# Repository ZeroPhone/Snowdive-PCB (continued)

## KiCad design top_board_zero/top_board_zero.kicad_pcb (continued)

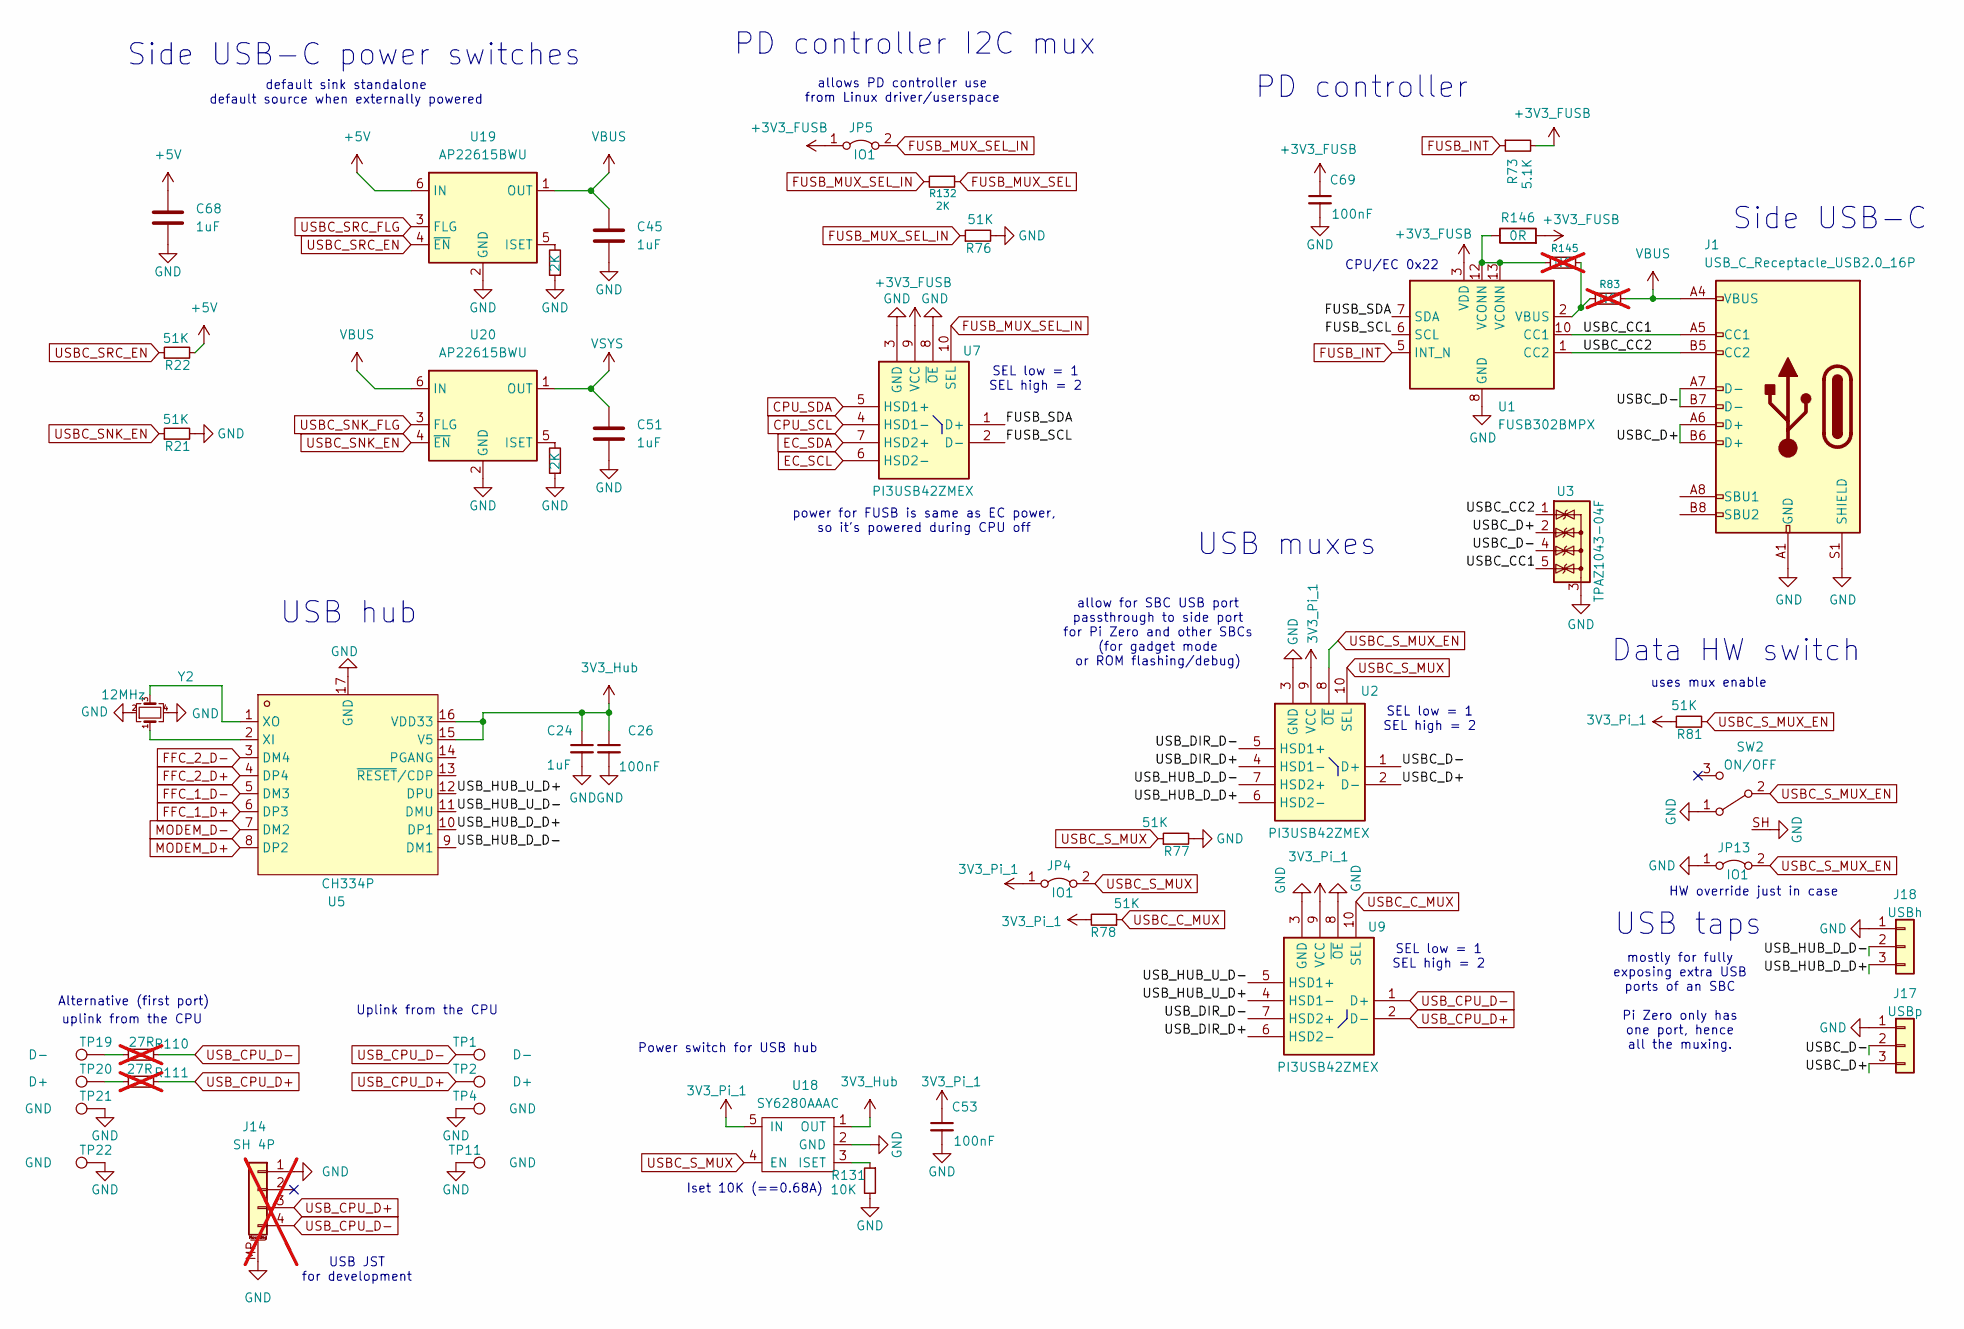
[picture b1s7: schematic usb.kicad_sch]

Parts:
C24: 1uF; C_0402_1005Metric; LCSC Part C52923
C26, C53, C69: 100nF; C_0402_1005Metric; LCSC Part C1525
C45, C51, C68: 1uF; C_0805_2012Metric_Pad1.18x1.45mm_HandSolder
J1: USB_C_Receptacle_USB2.0_16P; USB_C_Receptacle_HRO_TYPE-C-31-M-12; LCSC Part C165948
J14: SH 4P; JST_SH_SM04B-SRSS-TB_1x04-1MP_P1.00mm_Horizontal; LCSC Part C970137; not fitted
J17: USBp; PinHeader_1x03_P1.27mm_Vertical
J18: USBh; PinHeader_1x03_P1.27mm_Vertical
JP4, JP5, JP13: IO1; SolderJumper-2_smol_Open
R21, R22, R76, R77, R78, R81: 51K; R_0402_1005Metric; LCSC Part C25794
R73: 5.1K; R_0402_1005Metric; LCSC Part C25905
R83, R145: NC; R_0402_1005Metric; not fitted
R110, R111: 27R; R_0402_1005Metric; LCSC Part C25105; not fitted
R119, R120, R132: 2K; R_0402_1005Metric; LCSC Part C4109
R131: 10K; R_0402_1005Metric; LCSC Part C25744
R146: 0R; R_0402_1005Metric; LCSC Part C17168
SW2: ON/OFF; SW_SPDT_PCM12_SH; LCSC Part C431540
TP1, TP19: D-; TestPoint_Pad_1.0x1.0mm
TP2, TP20: D+; TestPoint_Pad_1.0x1.0mm
TP4, TP11, TP21, TP22: GND; TestPoint_Pad_1.0x1.0mm
U1: FUSB302BMPX; WQFN-14-1EP_2.5x2.5mm_P0.5mm_EP1.45x1.45mm
U2, U7, U9: PI3USB42ZMEX; QFN40P140X180X55-10N; Manufacturer_Part_Number FSUSB42UMX; Mouser Part Number 512-FSUSB42UMX
U3: TPAZ1043-04F; USON-10_2.5x1.0mm_P0.5mm
U5: CH334P; QFN-16-1EP_3x3mm_P0.5mm_EP1.7x1.7mm; LCSC Part C5373042
U18: SY6280AAAC; SOT-23-5; LCSC Part C207620
U19, U20: AP22615BWU; SOT-23-6
Y2: 12MHz; Crystal_SMD_3225-4Pin_3.2x2.5mm; LCSC Part C258938

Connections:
3V3_Hub: C24.1, C26.1, U5.15 (V5), U5.16 (VDD33), U18.1 (OUT); also elsewhere on the board
3V3_Pi_1: C53.1, JP4.1 (A), R78.2, R81.1, U2.9 (VCC), U9.9 (VCC), U18.5 (IN); also elsewhere on the board
+3V3_FUSB: C69.1, JP5.1 (A), R73.2, R146.2, U1.3 (VDD), U1.4 (VDD), U7.9 (VCC); also elsewhere on the board
+5V: C68.1, R22.2, U19.6 (IN); also elsewhere on the board
/USB/FUSB_SCL: U1.6 (SCL), U7.2 (D-)
/USB/FUSB_SDA: U1.7 (SDA), U7.1 (D+)
/USB/USBC_CC1: J1.A5 (CC1), U1.10 (CC1), U1.11 (CC1), U3.5 (IO4), U3.6 (NC)
/USB/USBC_CC2: J1.B5 (CC2), U1.1 (CC2), U1.14 (CC2), U3.1 (IO1), U3.10 (NC)
/USB/USBC_D+: J1.A6 (D+), J1.B6 (D+), J17.3, U2.2 (D-), U3.2 (IO2), U3.9 (NC)
/USB/USBC_D-: J1.A7 (D-), J1.B7 (D-), J17.2, U2.1 (D+), U3.4 (IO3), U3.7 (NC)
/USB/USB_DIR_D+: U2.4 (HSD1-), U9.6 (HSD2-)
/USB/USB_DIR_D-: U2.5 (HSD1+), U9.7 (HSD2+)
/USB/USB_HUB_D_D+: J18.3, U2.6 (HSD2-), U5.10 (DP1)
/USB/USB_HUB_D_D-: J18.2, U2.7 (HSD2+), U5.9 (DM1)
/USB/USB_HUB_U_D+: U5.12 (DPU), U9.4 (HSD1-)
/USB/USB_HUB_U_D-: U5.11 (DMU), U9.5 (HSD1+)
CPU_SCL: U7.4 (HSD1-); also elsewhere on the board
CPU_SDA: U7.5 (HSD1+); also elsewhere on the board
EC_SCL: U7.6 (HSD2-); also elsewhere on the board
EC_SDA: U7.7 (HSD2+); also elsewhere on the board
FFC_1_D+: U5.6 (DP3); also elsewhere on the board
FFC_1_D-: U5.5 (DM3); also elsewhere on the board
FFC_2_D+: U5.4 (DP4); also elsewhere on the board
FFC_2_D-: U5.3 (DM4); also elsewhere on the board
FUSB_INT: R73.1, U1.5 (INT_N); also elsewhere on the board
FUSB_MUX_SEL: R132.1; also elsewhere on the board
FUSB_MUX_SEL_IN: JP5.2 (B), R76.1, R132.2, U7.10 (SEL)
GND: C24.2, C26.2, C45.2, C51.2, C53.2, C68.2, C69.2, J1.A1 (GND), J1.A12 (GND), J1.B1 (GND), J1.B12 (GND), J1.S1 (SHIELD), J14.1, J14.MP (MountPin), J17.1, J18.1, JP13.1 (A), R21.2, R76.2, R77.2, R119.1, R120.1, R131.2, SW2.1 (A), SW2.SH, TP4.1 (1_1), TP11.1 (1_1), TP21.1 (1_1), TP22.1 (1_1), U1.8 (GND), U1.9 (GND), U1.15 (GND), U2.3 (GND), U3.3 (G), U3.8 (G), U5.17 (GND), U7.3 (GND), U7.8 (~OE), U9.3 (GND), U9.8 (~OE), U18.2 (GND), U19.2 (GND), U20.2 (GND), Y2.2, Y2.4; also elsewhere on the board
MODEM_D+: U5.8 (DP2); also elsewhere on the board
MODEM_D-: U5.7 (DM2); also elsewhere on the board
unnamed: R110.1, TP19.1 (1_1)
unnamed: R111.1, TP20.1 (1_1)
unnamed: R145.1, R146.1, U1.12 (VCONN), U1.13 (VCONN)
unnamed: R83.1, R145.2, U1.2 (VBUS)
unnamed: U5.2 (XI), Y2.1
unnamed: U5.1 (XO), Y2.3
unnamed: R131.1, U18.3 (ISET)
unnamed: R120.2, U19.5 (ISET)
unnamed: R119.2, U20.5 (ISET)
USBC_C_MUX: R78.1, U9.10 (SEL); also elsewhere on the board
USBC_SNK_EN: R21.1, U20.4 (~EN); also elsewhere on the board
USBC_SNK_FLG: U20.3 (FLG); also elsewhere on the board
USBC_SRC_EN: R22.1, U19.4 (~EN); also elsewhere on the board
USBC_SRC_FLG: U19.3 (FLG); also elsewhere on the board
USBC_S_MUX: JP4.2 (B), R77.1, U2.10 (SEL), U18.4 (EN); also elsewhere on the board
USBC_S_MUX_EN: JP13.2 (B), R81.2, SW2.2 (B), U2.8 (~OE)
USB_CPU_D+: J14.3, R111.2, TP2.1 (1_1), U9.2 (D-)
USB_CPU_D-: J14.4, R110.2, TP1.1 (1_1), U9.1 (D+)
VBUS: C45.1, J1.A4 (VBUS), J1.A9 (VBUS), J1.B4 (VBUS), J1.B9 (VBUS), R83.2, U19.1 (OUT), U20.6 (IN)
VSYS: C51.1, U20.1 (OUT); also elsewhere on the board

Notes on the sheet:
allow for SBC USB port passthrough to side port for Pi Zero and other SBCs (for gadget mode or ROM flashing/debug)
CPU/EC 0x22
USB taps
PD controller
Power switch for USB hub
Side USB-C
Uplink from the CPU
SEL low = 1 SEL high = 2
Side USB-C power switches
default sink standalone default source when externally powered
PD controller I2C mux
allows PD controller use from Linux driver/userspace
Data HW switch
uses mux enable
mostly for fully exposing extra USB ports of an SBC Pi Zero only has one port, hence all the muxing.
Alternative (first port)
USB muxes
HW override just in case
USB hub
USB JST for development
power for FUSB is same as EC power, so it's powered during CPU off
uplink from the CPU
Iset 10K (==0.68A)

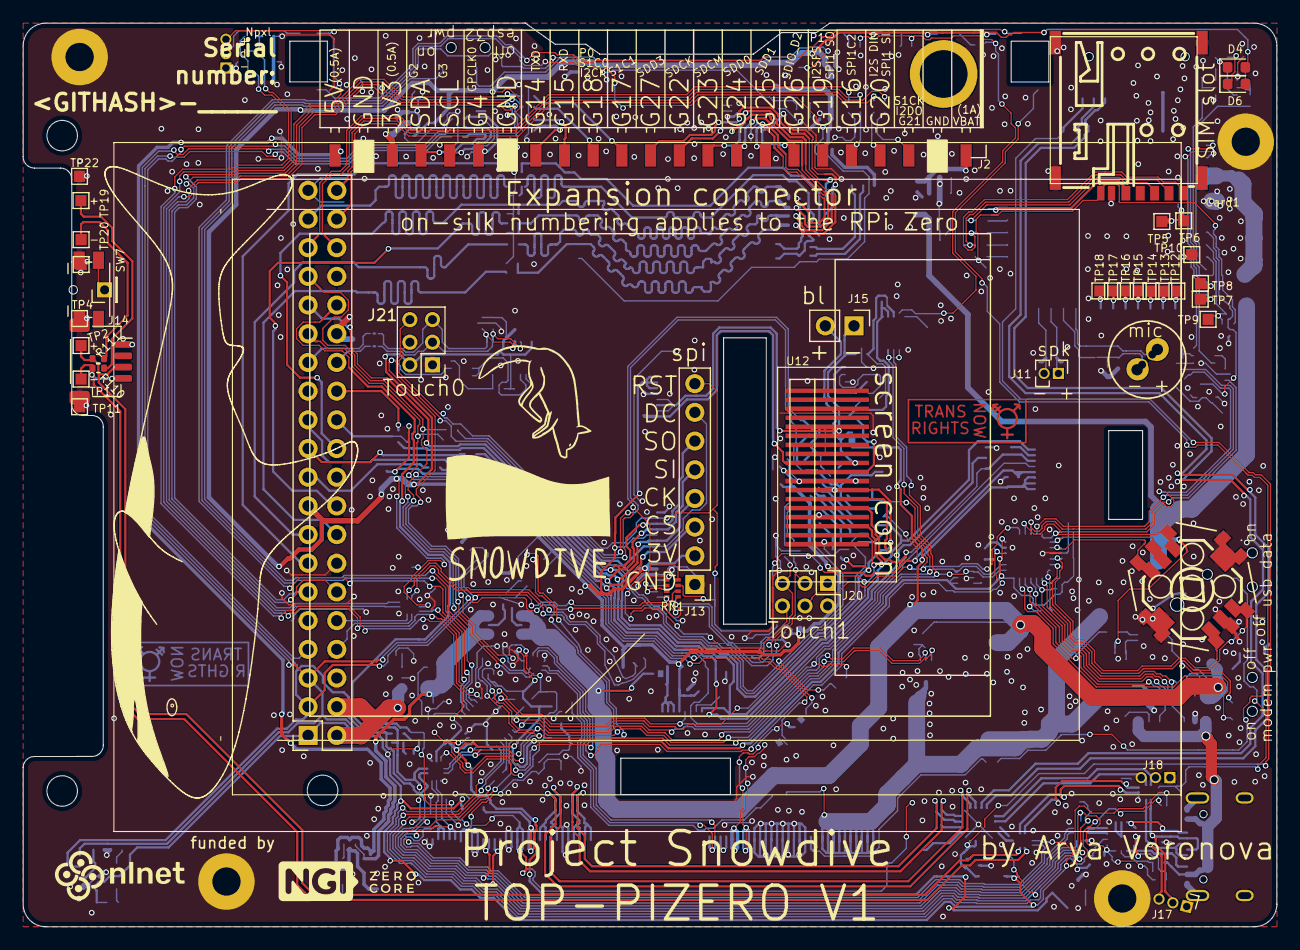
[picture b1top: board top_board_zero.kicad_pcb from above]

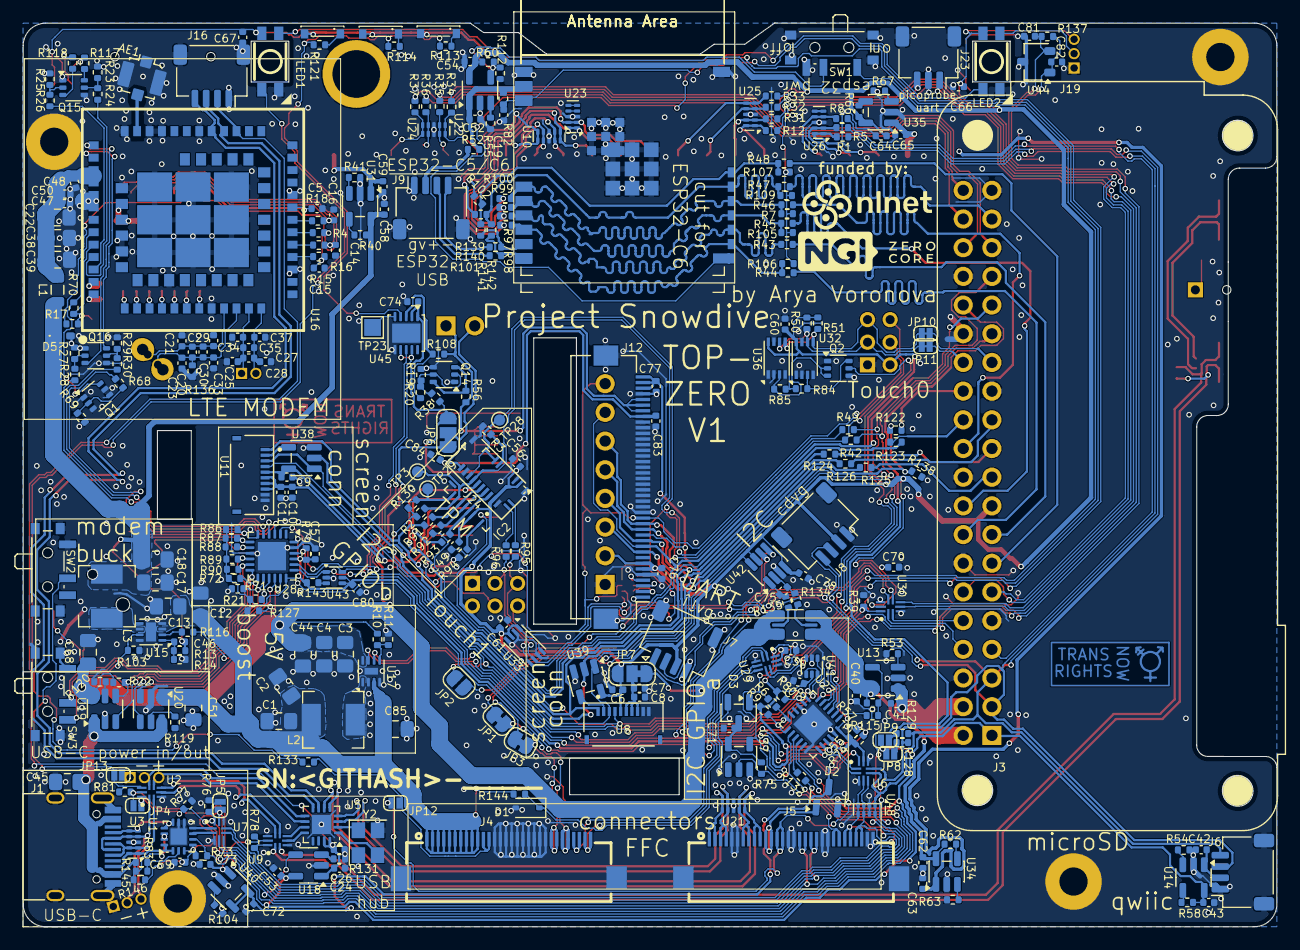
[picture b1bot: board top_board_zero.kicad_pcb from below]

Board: 4 copper layers, 111.0 x 80.0 mm, 372 parts (323 on the bottom side), 260 nets.

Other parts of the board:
TRNSRTS: Trans Rights now Front
TRNSRTS#2: Trans Rights now Back

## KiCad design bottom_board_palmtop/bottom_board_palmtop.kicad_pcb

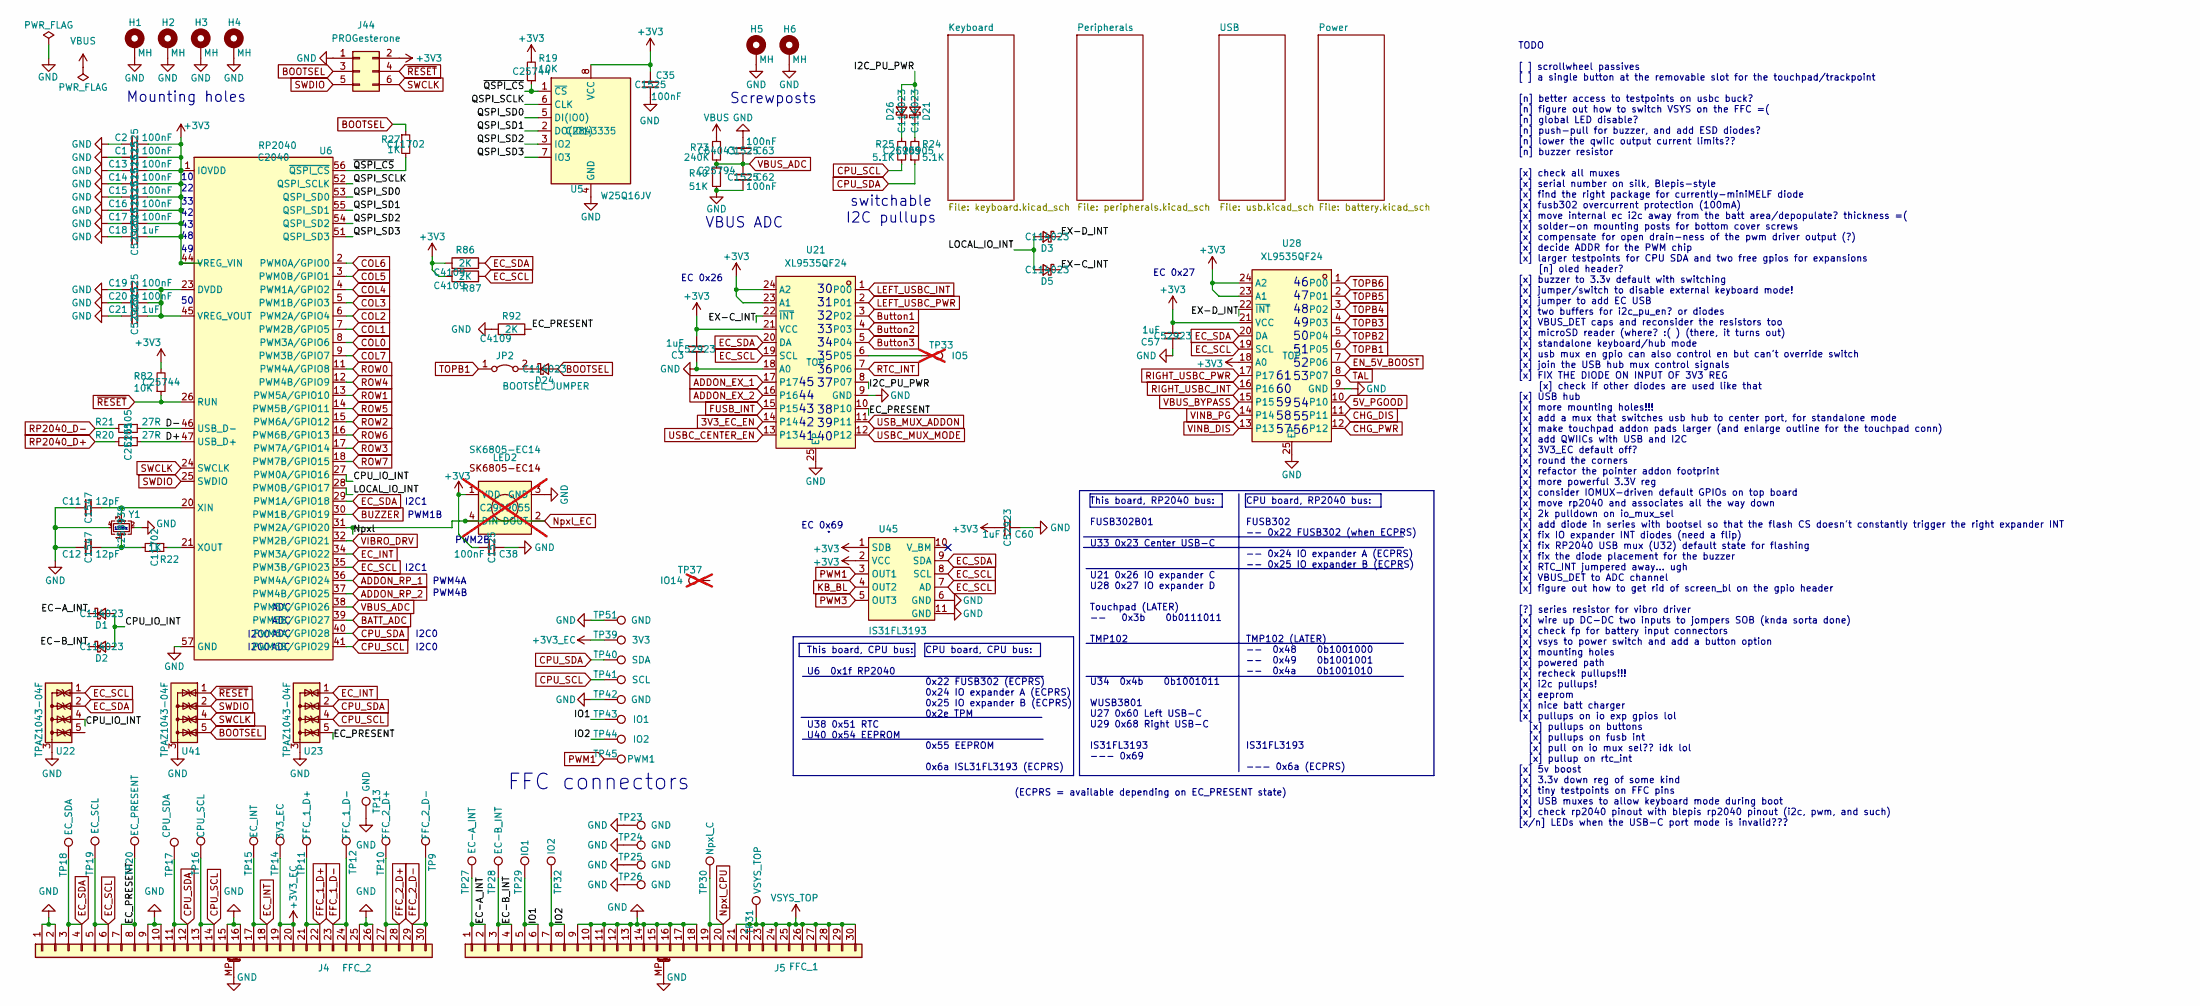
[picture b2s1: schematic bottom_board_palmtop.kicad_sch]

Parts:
C1, C2, C13, C14, C15, C16, C17, C19, C20, C35, C38, C62, C63: 100nF; C_0402_1005Metric; LCSC Part C1525
C3, C18, C21, C57, C60: 1uF; C_0402_1005Metric; LCSC Part C52923
C11, C12: 12pF; C_0402_1005Metric; LCSC Part C1547
D1, D2, D3, D5, D21, D24, D26: D_Schottky_Small; D_SOD-323; LCSC Part C114023
H1, H2, H3, H4: MH; MountingHole_2.5mm_Pad
H5, H6: MH; MountingHole_2.5mm_Pad-paste
J4: FFC_2; FPC-SMD_30P-P0.50_XF3M-3015-1B; LCSC Part C5700582
J5: FFC_1; FPC-SMD_30P-P0.50_XF3M-3015-1B; LCSC Part C5700582
J44: PROGesterone; PinHeader_2x03_P2.54mm_Vertical_PROG
JP2: BOOTSEL_JUMPER; SolderJumper-2_P1.3mm_Bridged_RoundedPad1.0x1.5mm
LED2: SK6805-EC14; LCSC Part C2909055; not fitted
R19, R82: 10K; R_0402_1005Metric; LCSC Part C25744
R20, R21: 27R; R_0402_1005Metric; LCSC Part C25105
R22, R27: 1K; R_0402_1005Metric; LCSC Part C11702
R24, R25: 5.1K; R_0402_1005Metric; LCSC Part C25905
R40: 51K; R_0402_1005Metric; LCSC Part C25794
R73: 240K; R_0402_1005Metric; LCSC Part C64043
R86, R87, R92: 2K; R_0402_1005Metric; LCSC Part C4109
TP9: FFC_2_D-; TestPoint_Pad_0.6x0.6mm
TP10: FFC_2_D+; TestPoint_Pad_0.6x0.6mm
TP11: FFC_1_D+; TestPoint_Pad_0.6x0.6mm
TP12: FFC_1_D-; TestPoint_Pad_0.6x0.6mm
TP13, TP23, TP24, TP25, TP26: GND; TestPoint_Pad_0.6x0.6mm
TP14: 3V3_EC; TestPoint_Pad_0.6x0.6mm
TP15: EC_INT; TestPoint_Pad_0.6x0.6mm
TP16: CPU_SCL; TestPoint_Pad_0.6x0.6mm
TP17: CPU_SDA; TestPoint_Pad_0.6x0.6mm
TP18: EC_SDA; TestPoint_Pad_0.6x0.6mm
TP19: EC_SCL; TestPoint_Pad_0.6x0.6mm
TP20: EC_PRESENT; TestPoint_Pad_0.6x0.6mm
TP27: EC-A_INT; TestPoint_Pad_0.6x0.6mm
TP28: EC-B_INT; TestPoint_Pad_0.6x0.6mm
TP29: IO1; TestPoint_Pad_0.6x0.6mm
TP30: Npxl_C; TestPoint_Pad_0.6x0.6mm
TP31: VSYS_TOP; TestPoint_Pad_0.6x0.6mm
TP32: IO2; TestPoint_Pad_0.6x0.6mm
TP33: IO5; TestPoint_Pad_0.6x0.6mm; not fitted
TP37: IO14; TestPoint_Pad_0.6x0.6mm; not fitted
TP39: 3V3; TestPoint_Pad_1.5x1.5mm
TP40: SDA; TestPoint_Pad_1.5x1.5mm
TP41: SCL; TestPoint_Pad_1.5x1.5mm
TP42, TP51: GND; TestPoint_Pad_1.5x1.5mm
TP43: IO1; TestPoint_Pad_1.5x1.5mm
TP44: IO2; TestPoint_Pad_1.5x1.5mm
TP45: PWM1; TestPoint_Pad_1.5x1.5mm
U5: W25Q16JV; DFN-8-1EP_3x2mm_P0.5mm_EP1.3x1.5mm; LCSC Part C2843335
U6: RP2040; QFN-56-1EP_7x7mm_P0.4mm_EP5.6x5.6mm; LCSC Part C2040
U21, U28: XL9535QF24; QFN-24-1EP_4x4mm_P0.5mm_EP2.5x2.5mm; LCSC Part C5444301
U22, U23, U41: TPAZ1043-04F; USON-10_2.5x1.0mm_P0.5mm
U45: IS31FL3193; DFN-10-1EP_3x3mm_P0.5mm_EP1.7x2.5mm
Y1: 12MHz; Crystal_SMD_3225-4Pin_3.2x2.5mm; LCSC Part C258938

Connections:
3V3_EC_EN: U21.14; also elsewhere on the board
5V_PGOOD: U28.10; also elsewhere on the board
+3V3: C1.1, C2.1, C3.1, C13.1, C14.1, C15.1, C16.1, C17.1, C18.1, C35.1, C38.1, C57.1, C60.1, J44.2, LED2.1 (VDD), R19.2, R82.2, R86.1, R87.1, U5.8 (VCC), U6.1 (IOVDD), U6.10 (IOVDD), U6.22 (IOVDD), U6.33 (IOVDD), U6.42 (IOVDD), U6.43 (ADC_AVDD), U6.44 (VREG_VIN), U6.48 (USB_VDD), U6.49 (IOVDD), U21.21 (VCC), U21.23 (A1), U21.24 (A2), U28.18 (A0), U28.21 (VCC), U28.23 (A1), U28.24 (A2), U45.1 (SDB), U45.2 (VCC); also elsewhere on the board
+3V3_EC: J4.19, J4.20, TP14.1, TP39.1; also elsewhere on the board
/CPU_IO_INT: D1.2 (A), D2.2 (A), U6.27 (PWM0A/GPIO16), U22.4 (IO3), U22.7 (NC)
/D+: R20.1, U6.47 (USB_D+)
/D-: R21.1, U6.46 (USB_D-)
/EC-A_INT: D1.1 (K), J5.1, J5.2, TP27.1
/EC-B_INT: D2.1 (K), J5.3, J5.4, TP28.1
/EC_PRESENT: J4.7, J4.8, R92.2, TP20.1, U21.10, U23.5 (IO4), U23.6 (NC)
/EX-C_INT: D5.1 (K), U21.22 (~INT)
/EX-D_INT: D3.1 (K), U28.22 (~INT)
/I2C_PU_PWR: D21.2 (A), D26.2 (A), U21.8 (P07)
/IO1: J5.5, J5.6, TP29.1, TP43.1
/IO2: J5.7, J5.8, TP32.1, TP44.1
/LOCAL_IO_INT: D3.2 (A), D5.2 (A), U6.28 (PWM0B/GPIO17)
/QSPI_SCLK: U5.6 (CLK), U6.52 (QSPI_SCLK)
/QSPI_SD0: U5.5 (DI(IO0)), U6.53 (QSPI_SD0)
/QSPI_SD1: U5.2 (DO(IO1)), U6.55 (QSPI_SD1)
/QSPI_SD2: U5.3 (IO2), U6.54 (QSPI_SD2)
/QSPI_SD3: U5.7 (IO3), U6.51 (QSPI_SD3)
/~QSPI_CS: R19.1, R27.2, U5.1 (~CS), U6.56 (~QSPI_CS)
ADDON_EX_1: U21.17; also elsewhere on the board
ADDON_EX_2: U21.16; also elsewhere on the board
ADDON_RP_1: U6.36 (PWM4A/GPIO24); also elsewhere on the board
ADDON_RP_2: U6.37 (PWM4B/GPIO25); also elsewhere on the board
BATT_ADC: U6.39 (PWM5B/GPIO27); also elsewhere on the board
BOOTSEL: D24.2 (A), J44.3, R27.1, U41.5 (IO4), U41.6 (NC)
BUZZER: U6.30 (PWM1B/GPIO19); also elsewhere on the board
Button1: U21.3 (P02); also elsewhere on the board
Button2: U21.4 (P03); also elsewhere on the board
Button3: U21.5 (P04); also elsewhere on the board
CHG_DIS: U28.11; also elsewhere on the board
CHG_PWR: U28.12; also elsewhere on the board
COL0: U6.8 (PWM3A/GPIO6); also elsewhere on the board
COL1: U6.7 (PWM2B/GPIO5); also elsewhere on the board
COL2: U6.6 (PWM2A/GPIO4); also elsewhere on the board
COL3: U6.5 (PWM1B/GPIO3); also elsewhere on the board
COL4: U6.4 (PWM1A/GPIO2); also elsewhere on the board
COL5: U6.3 (PWM0B/GPIO1); also elsewhere on the board
COL6: U6.2 (PWM0A/GPIO0); also elsewhere on the board
COL7: U6.9 (PWM3B/GPIO7); also elsewhere on the board
CPU_SCL: J4.13, J4.14, R25.2, TP16.1, TP41.1, U6.41 (PWM6B/GPIO29), U23.4 (IO3), U23.7 (NC); also elsewhere on the board
CPU_SDA: J4.11, J4.12, R24.1, TP17.1, TP40.1, U6.40 (PWM6A/GPIO28), U23.2 (IO2), U23.9 (NC); also elsewhere on the board
EC_INT: J4.17, J4.18, TP15.1, U6.34 (PWM3A/GPIO22), U23.1 (IO1), U23.10 (NC)
EC_SCL: J4.5, J4.6, R87.2, TP19.1, U6.35 (PWM3B/GPIO23), U21.19 (SCL), U22.1 (IO1), U22.10 (NC), U28.19 (SCL), U45.7 (AD), U45.8 (SCL); also elsewhere on the board
EC_SDA: J4.3, J4.4, R86.2, TP18.1, U6.29 (PWM1A/GPIO18), U21.20 (DA), U22.2 (IO2), U22.9 (NC), U28.20 (DA), U45.9 (SDA); also elsewhere on the board
EN_5V_BOOST: U28.7 (P06); also elsewhere on the board
FFC_1_D+: J4.21, J4.22, TP11.1; also elsewhere on the board
FFC_1_D-: J4.23, J4.24, TP12.1; also elsewhere on the board
FFC_2_D+: J4.27, J4.28, TP10.1; also elsewhere on the board
FFC_2_D-: J4.29, J4.30, TP9.1; also elsewhere on the board
FUSB_INT: U21.15; also elsewhere on the board
GND: C1.2, C2.2, C3.2, C11.2, C12.2, C13.2, C14.2, C15.2, C16.2, C17.2, C18.2, C19.2, C20.2, C21.2, C35.2, C38.2, C57.2, C60.2, C62.2, C63.2, H1.1, H2.1, H3.1, H4.1, H5.1, H6.1, J4.1, J4.2, J4.9, J4.10, J4.15, J4.16, J4.25, J4.26, J4.MP (MountPin), J5.9, J5.10, J5.11, J5.12, J5.13, J5.14, J5.15, J5.16, J5.17, J5.18, J5.MP (MountPin), J44.1, LED2.3 (GND), R40.2, R92.1, TP13.1, TP23.1, TP24.1, TP25.1, TP26.1, TP42.1, TP51.1, U5.4 (GND), U6.19 (TESTEN), U6.57 (GND), U21.9 (GND), U21.18 (A0), U21.25 (EP), U22.3 (G), U22.8 (G), U23.3 (G), U23.8 (G), U28.9 (GND), U28.25 (EP), U41.3 (G), U41.8 (G), U45.6 (GND), U45.11 (GND), Y1.2, Y1.4; also elsewhere on the board
KB_BL: U45.4 (OUT2); also elsewhere on the board
LEFT_USBC_INT: U21.1 (P00); also elsewhere on the board
LEFT_USBC_PWR: U21.2 (P01); also elsewhere on the board
unnamed: C12.1, R22.2, Y1.1
unnamed: D21.1 (K), R24.2
unnamed: D24.1 (K), JP2.2 (B)
unnamed: D26.1 (K), R25.1
unnamed: C19.1, C20.1, C21.1, U6.23 (DVDD), U6.45 (VREG_VOUT), U6.50 (DVDD)
unnamed: C11.1, U6.20 (XIN), Y1.3
unnamed: R22.1, U6.21 (XOUT)
unnamed: TP33.1, U21.6 (P05)
unnamed: U22.5 (IO4), U22.6 (NC)
Npxl_CPU: J5.19, J5.20, TP30.1; also elsewhere on the board
Npxl_EC: LED2.2 (DOUT), LED2.4 (DIN), U6.31 (PWM2A/GPIO20); also elsewhere on the board
PWM1: TP45.1, U45.3 (OUT1)
PWM3: U45.5 (OUT3); also elsewhere on the board
RIGHT_USBC_INT: U28.16; also elsewhere on the board
RIGHT_USBC_PWR: U28.17; also elsewhere on the board
ROW0: U6.11 (PWM4A/GPIO8); also elsewhere on the board
ROW1: U6.13 (PWM5A/GPIO10); also elsewhere on the board
ROW2: U6.15 (PWM6A/GPIO12); also elsewhere on the board
ROW3: U6.17 (PWM7A/GPIO14); also elsewhere on the board
ROW4: U6.12 (PWM4B/GPIO9); also elsewhere on the board
ROW5: U6.14 (PWM5B/GPIO11); also elsewhere on the board
ROW6: U6.16 (PWM6B/GPIO13); also elsewhere on the board
ROW7: U6.18 (PWM7B/GPIO15); also elsewhere on the board
RP2040_D+: R20.2; also elsewhere on the board
RP2040_D-: R21.2; also elsewhere on the board
RTC_INT: U21.7 (P06); also elsewhere on the board
SWCLK: J44.6, U6.24 (SWCLK), U41.4 (IO3), U41.7 (NC)
SWDIO: J44.5, U6.25 (SWDIO), U41.2 (IO2), U41.9 (NC)
TAL: U28.8 (P07); also elsewhere on the board
TOPB1: JP2.1 (A), U28.6 (P05); also elsewhere on the board
TOPB2: U28.5 (P04); also elsewhere on the board
TOPB3: U28.4 (P03); also elsewhere on the board
TOPB4: U28.3 (P02); also elsewhere on the board
TOPB5: U28.2 (P01); also elsewhere on the board
TOPB6: U28.1 (P00); also elsewhere on the board
USBC_CENTER_EN: U21.13; also elsewhere on the board
USBC_MUX_MODE: U21.12; also elsewhere on the board
USB_MUX_ADDON: U21.11; also elsewhere on the board
VBUS: R73.1; also elsewhere on the board
VBUS_ADC: C62.1, C63.1, R40.1, R73.2, U6.38 (PWM5A/GPIO26)
VBUS_BYPASS: U28.15; also elsewhere on the board
VIBRO_DRV: U6.32 (PWM2B/GPIO21); also elsewhere on the board
VINB_DIS: U28.13; also elsewhere on the board
VINB_PG: U28.14; also elsewhere on the board
VSYS_TOP: J5.21, J5.22, J5.23, J5.24, J5.25, J5.26, J5.27, J5.28, J5.29, J5.30, TP31.1; also elsewhere on the board
~RESET: J44.4, R82.1, U6.26 (RUN), U41.1 (IO1), U41.10 (NC)

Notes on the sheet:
EC 0x26
ADC
Mounting holes
PWM4B
PWM1B
I2C0
switchable I2C pullups
PWM4A
46 47 48 49 50 51 52 53 54 55 56
EC 0x69
30 31 32 33 34 35 36 37 38 39 40
(ECPRS = available depending on EC_PRESENT state)
This board, RP2040 bus: FUSB302B01 U33 0x23 Center USB-C U21 0x26 IO expander C U28 0x27 IO expander D Touchpad (LATER) -- 0x3b 0b0111011 TMP102 U34 0x4b 0b1001011 WUSB3801 U27 0x60 Left USB-C U29 0x68 Right USB-C IS31FL3193 --- 0x69
I2C0
FFC connectors
VBUS ADC
PWM2B
Screwposts
This board, CPU bus: U6 0x1f RP2040 U38 0x51 RTC U40 0x54 EEPROM
EC 0x27
TODO [ ] scrollwheel passives [ ] a single button at the removable slot for the touchpad/trackpoint [n] better access to testpoints on usbc buck? [n] figure out how to switch VSYS on the FFC =( [n] global LED disable? [n] push-pull for buzzer, and add ESD diodes? [n] lower the qwiic output current 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
CPU board, CPU bus: 0x22 FUSB302 (ECPRS) 0x24 IO expander A (ECPRS) 0x25 IO expander B (ECPRS) 0x2e TPM 0x55 EEPROM 0x6a ISL31FL3193 (ECPRS)
61 60 59 58 57
I2C1
45 44 43 42 41
12MHz
CPU board, RP2040 bus: FUSB302 -- 0x22 FUSB302 (when ECPRS) -- 0x24 IO expander A (ECPRS) -- 0x25 IO expander B (ECPRS) TMP102 (LATER) -- 0x48 0b1001000 -- 0x49 0b1001001 -- 0x4a 0b1001010 IS31FL3193 --- 0x6a (ECPRS)
nice

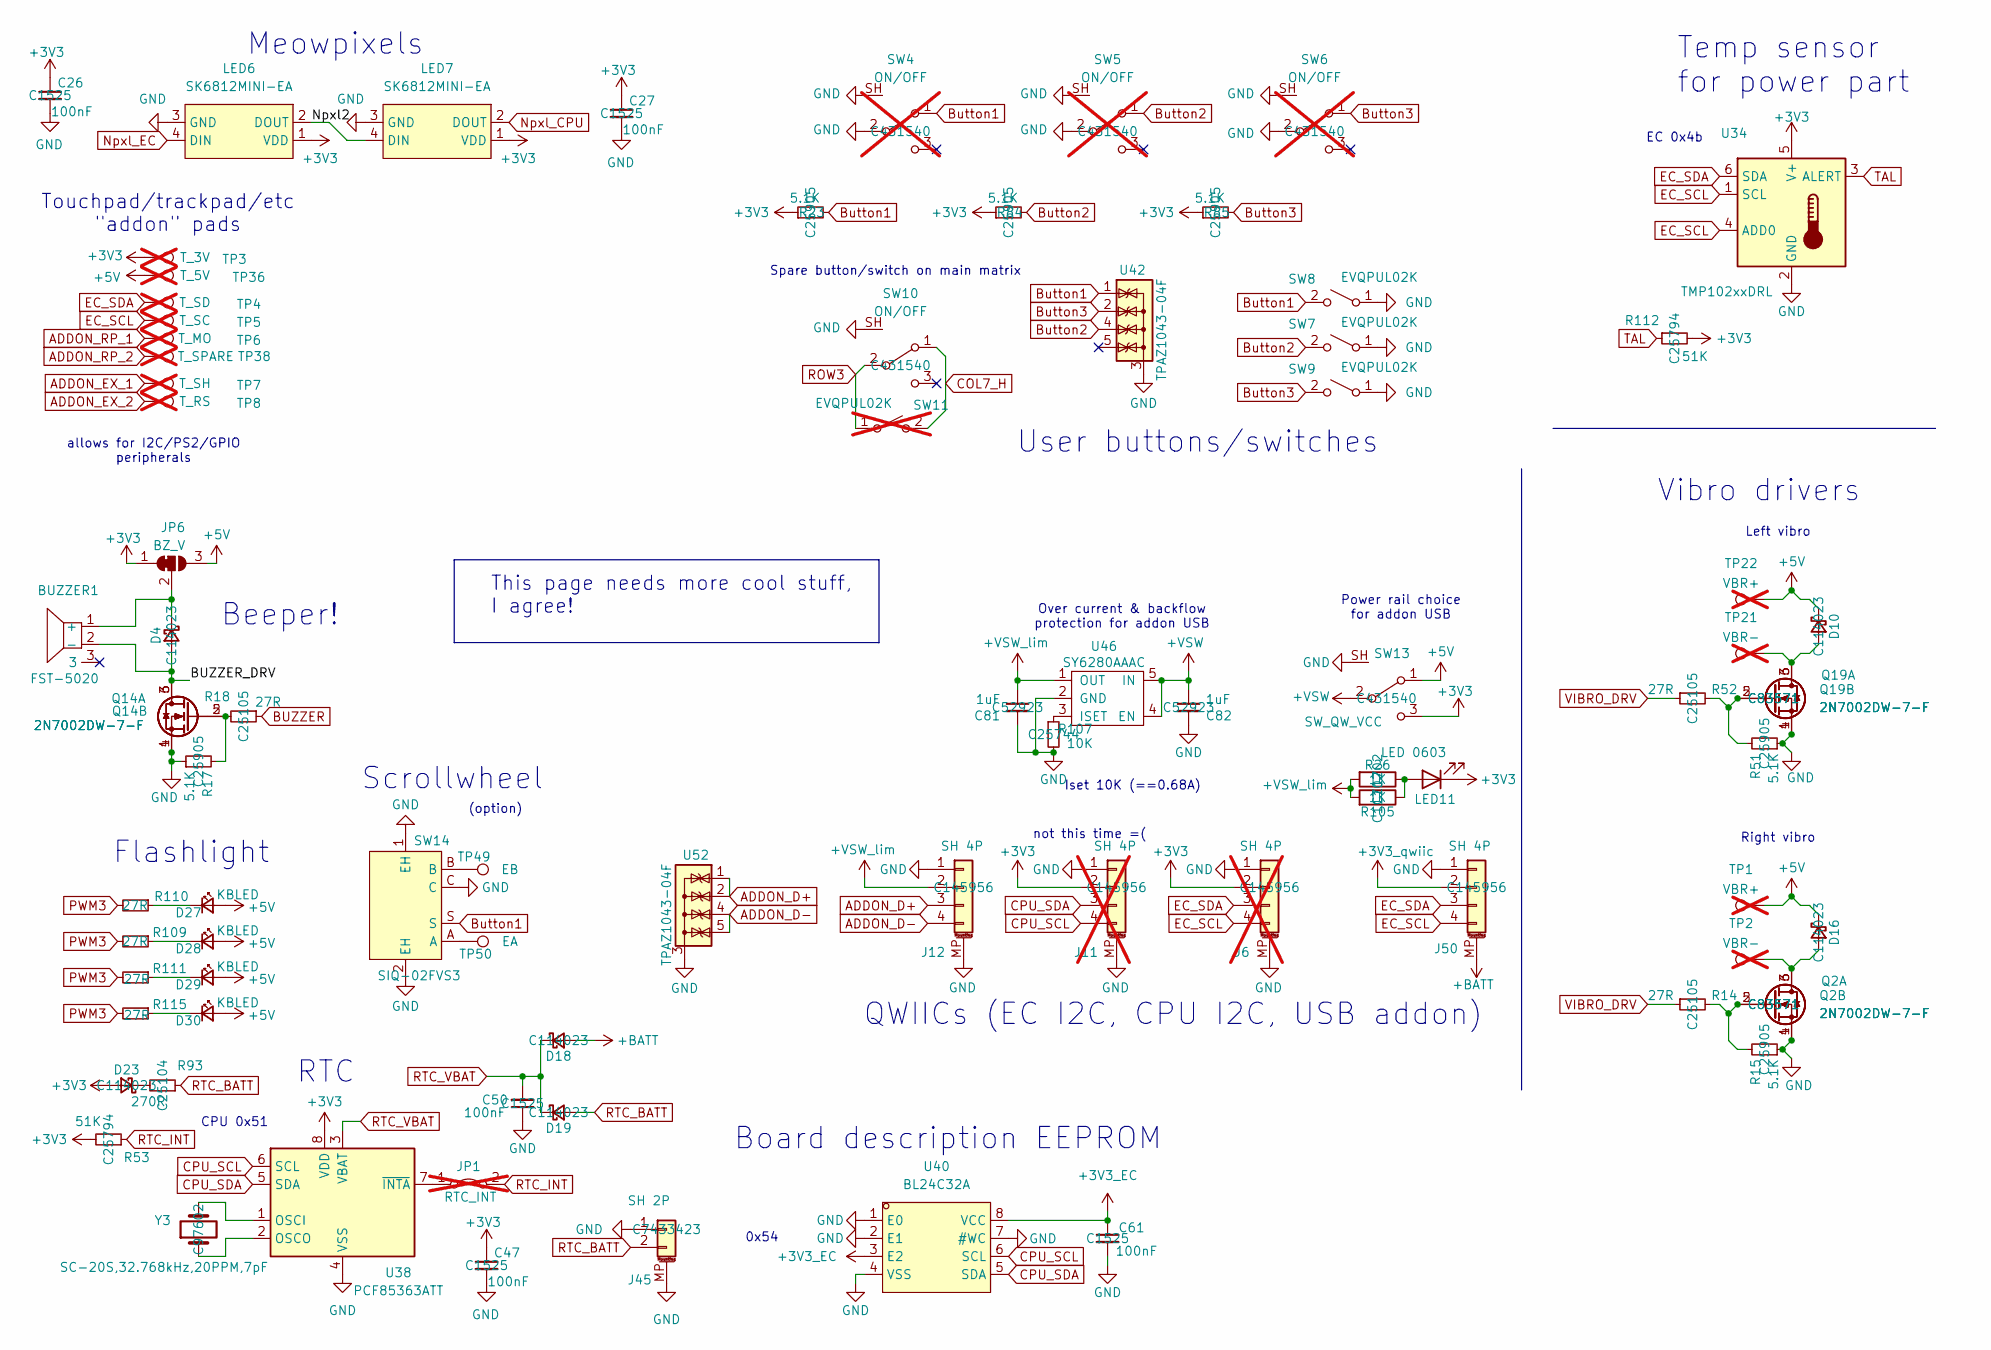
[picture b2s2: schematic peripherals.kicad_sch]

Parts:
BUZZER1: FST-5020; BUZ-SMD_FST-5020; LCSC Part C391029
C26, C27, C47, C50, C61: 100nF; C_0402_1005Metric; LCSC Part C1525
C81, C82: 1uF; C_0402_1005Metric; LCSC Part C52923
D4, D10, D16, D18, D19, D23: D_Schottky_Small; D_SOD-323; LCSC Part C114023
D27, D28, D29, D30: KBLED; LTW-010DCG
J6, J11: SH 4P; JST_SH_SM04B-SRSS-TB_1x04-1MP_P1.00mm_Horizontal; LCSC Part C145956; not fitted
J12, J50: SH 4P; JST_SH_SM04B-SRSS-TB_1x04-1MP_P1.00mm_Horizontal; LCSC Part C145956
J45: SH 2P; JST_SH_BM02B-SRSS-TB_1x02-1MP_P1.00mm_Vertical; LCSC Part C7433423
JP1: RTC_INT; SolderJumper-2_smol_Open; not fitted
JP6: BZ_V; SolderJumper-3_P1.3mm_Bridged12_RoundedPad1.0x1.5mm
LED6, LED7: SK6812MINI-EA; LED-SMD_4P-L3.2-W2.8_SK6812MINI-EA; LCSC Part C5378731
LED11: LED 0603; LED_0603_1608Metric; LCSC Part C5151483
Q2, Q14, Q19: 2N7002DW-7-F; SOT-363_SC-70-6; LCSC Part C83571
R14, R18, R52, R109, R110, R111, R115: 27R; R_0402_1005Metric; LCSC Part C25105
R15, R17, R23, R51, R84, R85: 5.1K; R_0402_1005Metric; LCSC Part C25905
R26, R105: 1K; R_0402_1005Metric; LCSC Part C11702
R53, R112: 51K; R_0402_1005Metric; LCSC Part C25794
R93: 270R; R_0402_1005Metric; LCSC Part C25104
R107: 10K; R_0402_1005Metric; LCSC Part C25744
SW4, SW5, SW6: ON/OFF; SW_SPDT_PCM12_SH; LCSC Part C431540; not fitted
SW7, SW8, SW9: EVQPUL02K; Panasonic_EVQPUL_EVQPUC
SW10: ON/OFF; SW_SPDT_PCM12_SH; LCSC Part C431540
SW11: EVQPUL02K; Panasonic_EVQPUL_EVQPUC; not fitted
SW13: SW_QW_VCC; SW_SPDT_PCM12_SH; LCSC Part C431540
SW14: SIQ-02FVS3; SW-SMD_SIQ-02FVS3; MPN SIQ-02FVS3; LCSC Part C29780879
TP1, TP22: VBR+; TestPoint_Pad_1.0x1.0mm; not fitted
TP2, TP21: VBR-; TestPoint_Pad_1.0x1.0mm; not fitted
TP3: T_3V; TestPoint_Pad_1.0x1.0mm; not fitted
TP4: T_SD; TestPoint_Pad_1.0x1.0mm; not fitted
TP5: T_SC; TestPoint_Pad_1.0x1.0mm; not fitted
TP6: T_MO; TestPoint_Pad_1.0x1.0mm; not fitted
TP7: T_SH; TestPoint_Pad_1.0x1.0mm; not fitted
TP8: T_RS; TestPoint_Pad_1.0x1.0mm; not fitted
TP36: T_5V; TestPoint_Pad_1.0x1.0mm; not fitted
TP38: T_SPARE; TestPoint_Pad_1.0x1.0mm; not fitted
TP49: EB; TestPoint_Pad_1.5x1.5mm
TP50: EA; TestPoint_Pad_1.5x1.5mm
U34: TMP102xxDRL; SOT-563; LCSC Part C99269
U38: PCF85363ATT; TSSOP-8_3x3mm_P0.65mm
U40: BL24C32A; DFN-8-1EP_3x2mm_P0.5mm_EP1.3x1.5mm; LCSC Part C691878
U42, U52: TPAZ1043-04F; USON-10_2.5x1.0mm_P0.5mm
U46: SY6280AAAC; SOT-23-5; LCSC Part C207620
Y3: SC-20S,32.768kHz,20PPM,7pF; Crystal_SMD_TXC_9HT11-2Pin_2.0x1.2mm; LCSC Part C97602

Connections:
+3V3: C26.1, C27.1, C47.1, D23.2 (A), J6.2, J11.2, JP6.1 (A), LED6.1 (VDD), LED7.1 (VDD), LED11.1 (K), R23.1, R53.2, R84.1, R85.1, R112.2, SW13.3 (C), TP3.1, U34.5 (V+), U38.8 (VDD); also elsewhere on the board
+3V3_EC: C61.1, U40.3 (E2), U40.8 (VCC); also elsewhere on the board
+3V3_qwiic: J50.2; also elsewhere on the board
+5V: D10.1 (K), D16.1 (K), D27.2 (A), D28.2 (A), D29.2 (A), D30.2 (A), JP6.3 (B), SW13.1 (A), TP1.1, TP22.1, TP36.1; also elsewhere on the board
+BATT: D18.2 (A), J50.MP (MountPin); also elsewhere on the board
+VSW: C82.1, SW13.2 (B), U46.4 (EN), U46.5 (IN)
+VSW_lim: C81.1, J12.2, R26.2, R105.2, U46.1 (OUT)
/Peripherals/BUZZER_DRV: BUZZER1.2 (-), D4.2 (A), Q14.3 (D), Q14.6 (D)
/Peripherals/Npxl2: LED6.2 (DOUT), LED7.4 (DIN)
ADDON_D+: J12.3, U52.1 (IO1), U52.2 (IO2), U52.9 (NC), U52.10 (NC); also elsewhere on the board
ADDON_D-: J12.4, U52.4 (IO3), U52.5 (IO4), U52.6 (NC), U52.7 (NC); also elsewhere on the board
ADDON_EX_1: TP7.1; also elsewhere on the board
ADDON_EX_2: TP8.1; also elsewhere on the board
ADDON_RP_1: TP6.1; also elsewhere on the board
ADDON_RP_2: TP38.1; also elsewhere on the board
BUZZER: R18.1; also elsewhere on the board
Button1: R23.2, SW4.1 (A), SW8.2 (B), SW14.S, U42.1 (IO1), U42.10 (NC); also elsewhere on the board
Button2: R84.2, SW5.1 (A), SW7.2 (B), U42.4 (IO3), U42.7 (NC); also elsewhere on the board
Button3: R85.2, SW6.1 (A), SW9.2 (B), U42.2 (IO2), U42.9 (NC); also elsewhere on the board
COL7_H: SW10.1 (A), SW11.2 (B); also elsewhere on the board
CPU_SCL: J11.4, U38.6 (SCL), U40.6 (SCL); also elsewhere on the board
CPU_SDA: J11.3, U38.5 (SDA), U40.5 (SDA); also elsewhere on the board
EC_SCL: J6.4, J50.4, TP5.1, U34.1 (SCL), U34.4 (ADD0); also elsewhere on the board
EC_SDA: J6.3, J50.3, TP4.1, U34.6 (SDA); also elsewhere on the board
GND: C26.2, C27.2, C47.2, C50.1, C61.2, C81.2, C82.2, J6.1, J6.MP (MountPin), J11.1, J11.MP (MountPin), J12.1, J12.MP (MountPin), J45.1, J45.MP (MountPin), J50.1, LED6.3 (GND), LED7.3 (GND), Q2.1 (S), Q2.4 (S), Q14.1 (S), Q14.4 (S), Q19.1 (S), Q19.4 (S), R15.1, R17.1, R51.1, R107.2, SW4.2 (B), SW4.SH, SW5.2 (B), SW5.SH, SW6.2 (B), SW6.SH, SW7.1 (A), SW8.1 (A), SW9.1 (A), SW10.SH, SW13.SH, SW14.1 (EH), SW14.2 (EH), SW14.C, U34.2 (GND), U38.4 (VSS), U40.1 (E0), U40.2 (E1), U40.4 (VSS), U40.7 (#WC), U42.3 (G), U42.8 (G), U46.2 (GND), U52.3 (G), U52.8 (G); also elsewhere on the board
unnamed: BUZZER1.1 (+), D4.1 (K), JP6.2 (C)
unnamed: D10.2 (A), Q19.3 (D), Q19.6 (D), TP21.1
unnamed: D16.2 (A), Q2.3 (D), Q2.6 (D), TP2.1
unnamed: D23.1 (K), R93.2
unnamed: D27.1 (K), R110.1
unnamed: D28.1 (K), R109.1
unnamed: D29.1 (K), R111.1
unnamed: D30.1 (K), R115.1
unnamed: JP1.1 (A), U38.7 (~INTA)
unnamed: LED11.2 (A), R26.1, R105.1
unnamed: Q2.2 (G), Q2.5 (G), R14.2, R15.2
unnamed: Q14.2 (G), Q14.5 (G), R17.2, R18.2
unnamed: Q19.2 (G), Q19.5 (G), R51.2, R52.2
unnamed: SW14.A, TP50.1
unnamed: SW14.B, TP49.1
unnamed: U38.1 (OSCI), Y3.2
unnamed: U38.2 (OSCO), Y3.1
unnamed: R107.1, U46.3 (ISET)
Npxl_CPU: LED7.2 (DOUT); also elsewhere on the board
Npxl_EC: LED6.4 (DIN); also elsewhere on the board
PWM3: R109.2, R110.2, R111.2, R115.2; also elsewhere on the board
ROW3: SW10.2 (B), SW11.1 (A); also elsewhere on the board
RTC_BATT: D19.2 (A), J45.2, R93.1
RTC_INT: JP1.2 (B), R53.1; also elsewhere on the board
RTC_VBAT: C50.2, D18.1 (K), D19.1 (K), U38.3 (VBAT)
TAL: R112.1, U34.3 (ALERT); also elsewhere on the board
VIBRO_DRV: R14.1, R52.1; also elsewhere on the board

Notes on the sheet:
Meowpixels
Iset 10K (==0.68A)
Flashlight
Over current & backflow protection for addon USB
CPU 0x51
Temp sensor for power part
not this time =(
Vibro drivers
Right vibro
Board description EEPROM
RTC
0x54
Scrollwheel
Beeper!
QWIICs (EC I2C, CPU I2C, USB addon)
EC 0x4b
Left vibro
User buttons/switches
(option)
Spare button/switch on main matrix
allows for I2C/PS2/GPIO peripherals
Touchpad/trackpad/etc "addon" pads
Power rail choice for addon USB
This page needs more cool stuff, I agree!
